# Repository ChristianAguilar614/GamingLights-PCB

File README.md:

# GamingLights-PCB
Arduino Nano Shield

Circuit utilizes the compact size of the Arduino Nano to round appropriate light controllers. This works as an accent lighting system with RGB custimization. 
MOSFET drivers help boost the current and voltage which will be used to amplifier the overall wattage of the system to support 24 watts

#3d View

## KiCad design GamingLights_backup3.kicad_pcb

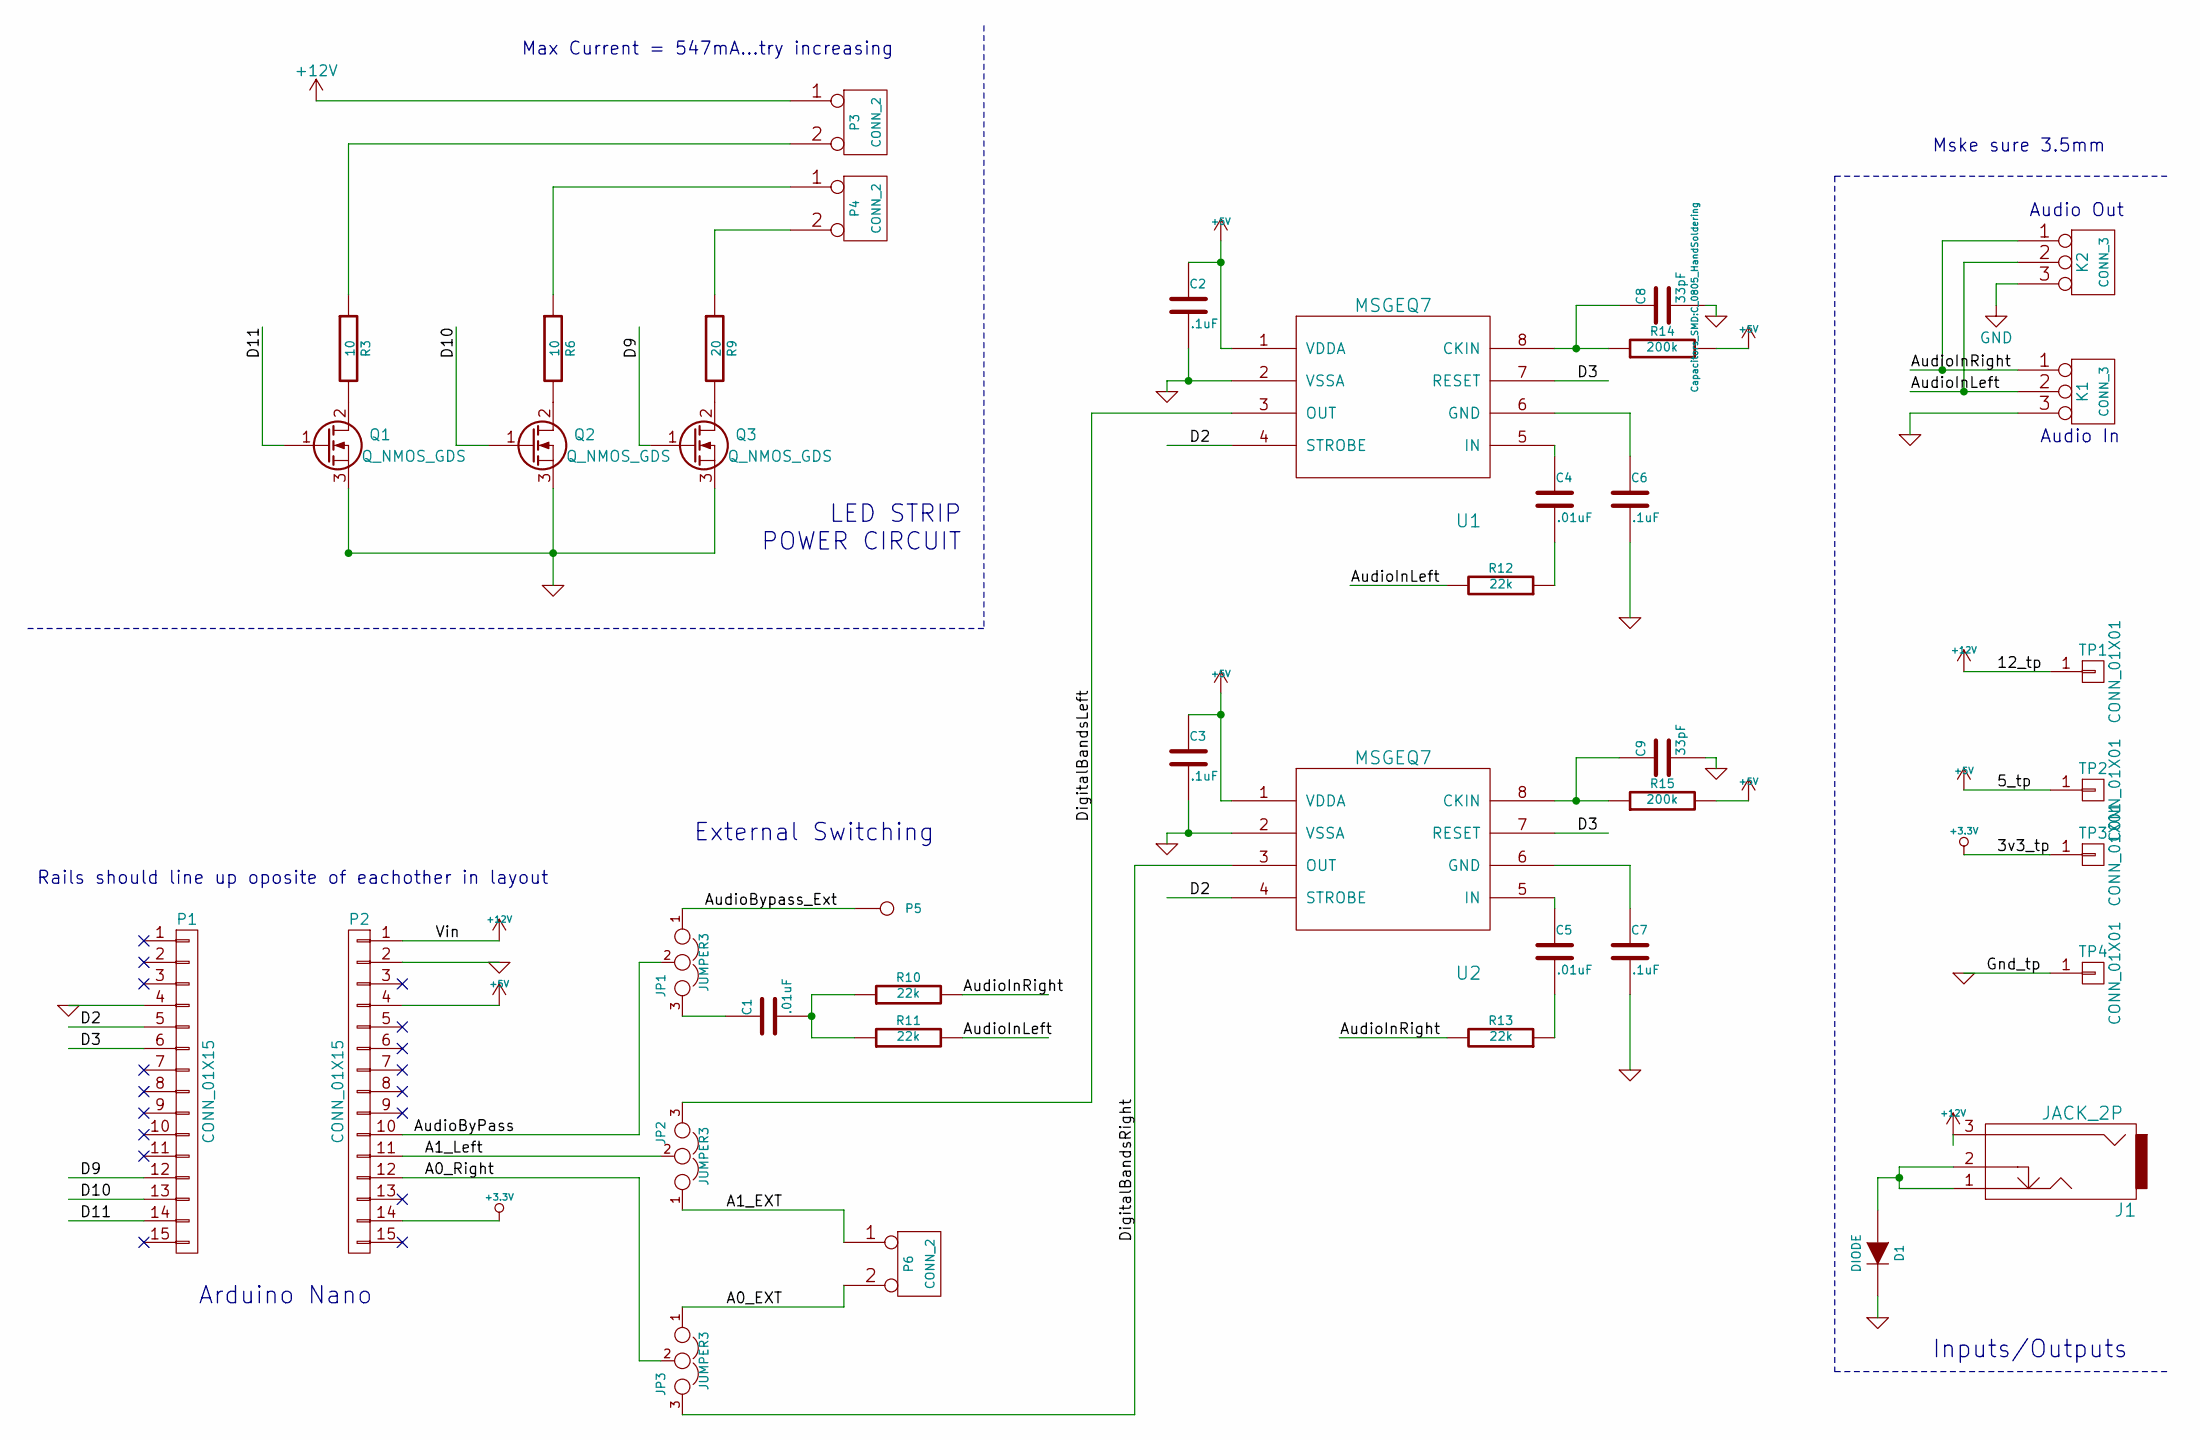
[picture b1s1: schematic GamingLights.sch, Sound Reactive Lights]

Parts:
C1, C4, C5: .01uF; C_0805_HandSoldering
C2, C3, C6, C7: .1uF; C_0805_HandSoldering
C8, C9: 33pF; C_0805_HandSoldering
D1: DIODE; Diode_DO-41_SOD81_Horizontal_RM10
J1: JACK_2P; BARREL_JACK
JP1, JP2, JP3: JUMPER3; Pin_Header_Straight_1x03
K1, K2: CONN_3; AudioJack
P1, P2: CONN_01X15; Socket_Strip_Straight_1x15
P3, P4, P6: CONN_2; Pin_Header_Straight_1x02
P5: CONN_1; Pin_Header_Straight_1x01
Q1, Q2, Q3: Q_NMOS_GDS; SOT-223
R3, R6: 10; R_1206_HandSoldering
R9: 20; R_1206_HandSoldering
R10, R11, R12, R13: 22k; R_1206_HandSoldering
R14, R15: 200k; R_1206_HandSoldering
TP1, TP2, TP3, TP4: CONN_01X01; Pin_Header_Straight_1x01
U1, U2: MSGEQ7; DIP-8_W7.62mm

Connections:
+3.3V: P2.14, TP3.1
+5V: C2.1, C3.1, P2.4, R14.2, R15.2, TP2.1, U1.1 (VDDA), U2.1 (VDDA)
+12V: J1.3, P2.1, P3.1, TP1.1
/A0_EXT: JP3.1, P6.2 (PM)
/A0_Right: JP3.2, P2.12
/A1_EXT: JP2.1, P6.1
/A1_Left: JP2.2, P2.11
/AudioByPass: JP1.2, P2.10
/AudioBypass_Ext: JP1.1, P5.1
/AudioInLeft: K1.2 (PM), K2.2 (PM), R11.2, R12.2
/AudioInRight: K1.1, K2.1, R10.2, R13.2
/D2: P1.5, U1.4 (STROBE), U2.4 (STROBE)
/D3: P1.6, U1.7 (RESET), U2.7 (RESET)
/D9: P1.12, Q3.1 (G)
/D10: P1.13, Q2.1 (G)
/D11: P1.14, Q1.1 (G)
/DigitalBandsLeft: JP2.3, U1.3 (OUT)
/DigitalBandsRight: JP3.3, U2.3 (OUT)
GND: C2.2, C3.2, C6.2, C7.2, C8.2, C9.2, D1.2 (K), K1.3, K2.3, P1.4, P2.2, Q1.3 (S), Q2.3 (S), Q3.3 (S), TP4.1, U1.2 (VSSA), U2.2 (VSSA)
unnamed: C1.1, JP1.3
unnamed: C1.2, R10.1, R11.1
unnamed: C4.1, U1.5 (IN)
unnamed: C4.2, R12.1
unnamed: C5.1, U2.5 (IN)
unnamed: C5.2, R13.1
unnamed: C6.1, U1.6 (GND)
unnamed: C7.1, U2.6 (GND)
unnamed: C8.1, R14.1, U1.8 (CKIN)
unnamed: C9.1, R15.1, U2.8 (CKIN)
unnamed: D1.1 (A), J1.1, J1.2
unnamed: P3.2 (PM), R3.1
unnamed: P4.1, R6.1
unnamed: P4.2 (PM), R9.1
unnamed: Q1.2 (D), R3.2
unnamed: Q2.2 (D), R6.2
unnamed: Q3.2 (D), R9.2

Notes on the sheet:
LED STRIP POWER CIRCUIT
Arduino Nano
Inputs/Outputs
External Switching
Audio Out
Audio In
Rails should line up oposite of eachother in layout
Mske sure 3.5mm
Max Current = 547mA...try increasing

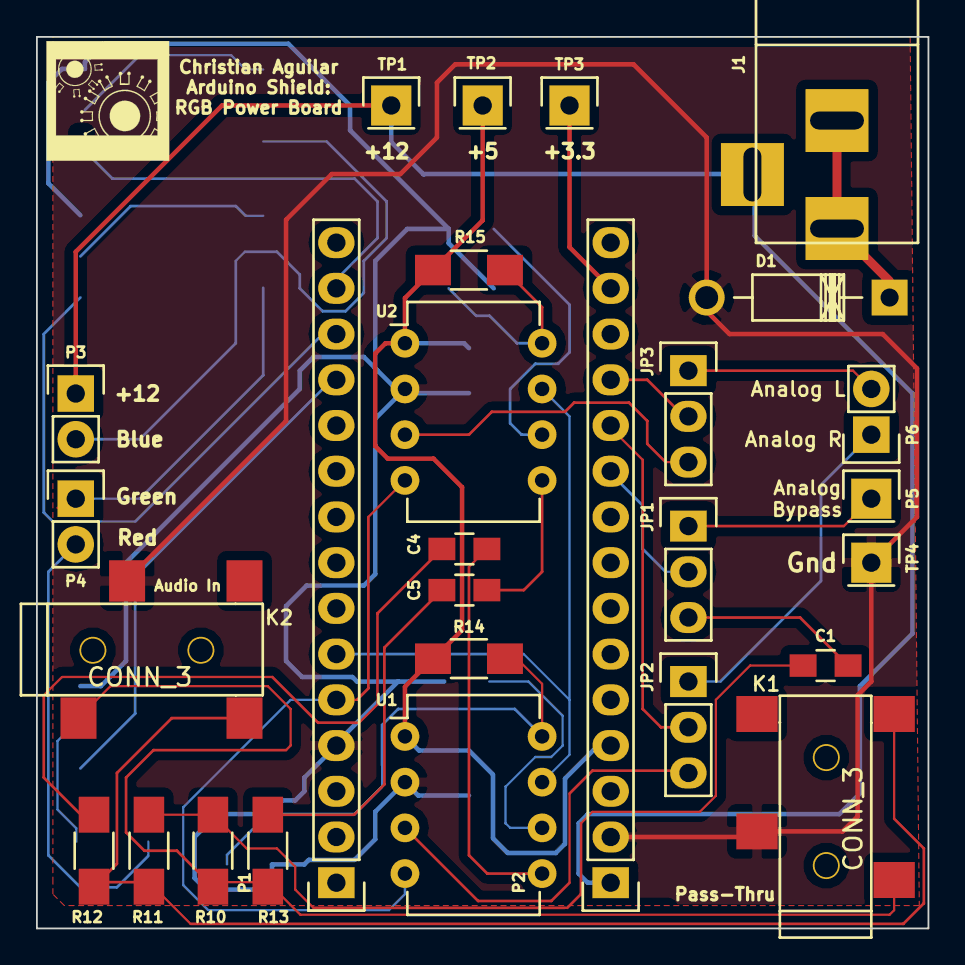
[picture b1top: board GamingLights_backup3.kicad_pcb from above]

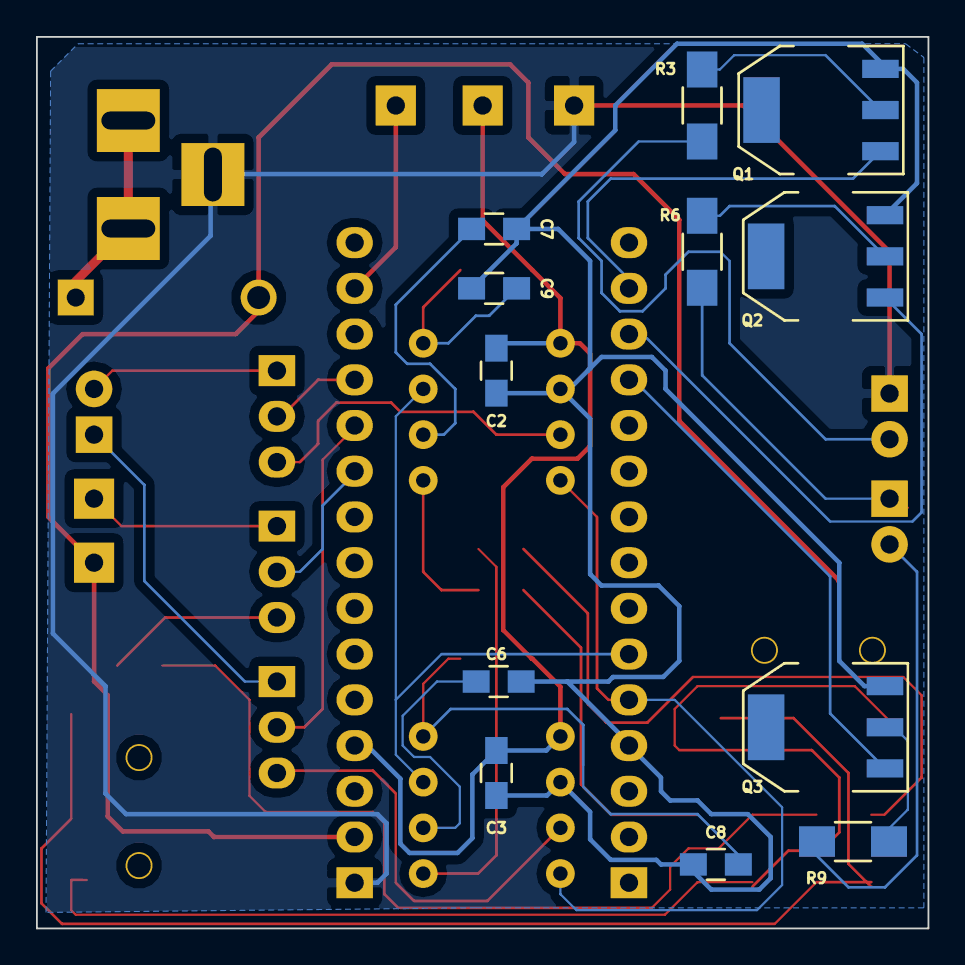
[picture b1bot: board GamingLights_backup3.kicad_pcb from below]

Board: 2 copper layers, 49.5 x 49.5 mm, 40 parts (12 on the bottom side), 36 nets.

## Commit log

2017-03-08 Initial Upload
2017-03-08 readme update
2017-03-09 Unnecessary files deleted
